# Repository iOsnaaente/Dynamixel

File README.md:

# Dynamixel

Dispositório pessoal para guardar códigos para Atuadores Dynamixel.

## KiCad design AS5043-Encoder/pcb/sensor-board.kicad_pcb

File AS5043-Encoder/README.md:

AS5043-Encoder
==============

This repos contains all the plans and software necessary to build a magnetic rotary encoder using the AS4053.

The setup for this chip is rather simple,
you need a few external components and a neodymium magnet that is attached to your rotating axis.
Then the sensor is placed below the magnet.
Since it uses the magnetic field neither dirt nor light will be a problem.
The sensor will output the angle of the magnet relative to a programmable starting position via analogue output
or via a [SSI](https://en.wikipedia.org/wiki/Synchronous_Serial_Interface)-Style interface.
(See the datasheet for details.)
With 10bit resolution it should be theoretically possible to measure the current angle in 0.35° steps.

The guys at austria microsystems were kind enough to send me 3 AS5043 and 3 AS5030 (similar part 8bit resolution).
*Big thanks to them.*

Mechanical Parts
----------------
There are 2 plans available :

* A version that can be build using a lathe
* A 3D printable version created with open scad
* A 3D printable version created with freecad

The plans for the first version can be found in the repo directory [chasis/lathe](chasis/lathe).
You can simply print out the pdfs and hand them over to someone who has access to a lathe.
He or she should know what to do with them.

For the 3D printable versions simply run the stl files through your 3D printing toolchain.
The 3D printable versions can be found in [chasis/3d_printable_scad](chasis/3d_printable_scad)
and [chasis/3d_printable_freecad](chasis/3d_printable_freecad).

You will also need some M3 screws and nuts which you should find in your favorite hardware store.
For the magnets I'd recommend browsing ebay for 5mmx5mmx5mm neodym magnet cubes.
The ball bearing you'll need is a common 6200Z bearing.
Again try your hardware store or ebay.
There you'll possible also find some M3 5mm long distance bolts, that are used in the lathe version of the chassis.

Software
--------
The software part required some tricks to get it working.
Comparing the signal diagrams for SPI in Atmels datasheet and for *SSI* in the AS5043 a small problem becomes obvious.
The AS5043 needs a clock signal that is high in idle stage and the bits will be shifted out on the positive clock edge.
That sounds very much like the SPI mode 3 in Atmel-speech: Clock high on idle and data will be read on every rising edge.
Leaving us with one problem: The Atmel hardware SPI can read the miso pin only at a clock edge.
As mentioned before data is sampled at the rising edge for mode 3.
So shifting out and reading would be done almost synchronous and due to signal rise and fall times this will probably fail 90% of the time.

The solution is to use mode 2: Clock high on idle and bits are read at the falling edge.
Now we have a different problem.
The first bit will be read before it was shifted out by the AS5043.
Using AVR SPI it is possible to read one byte at time, so two read cycles are required to read the full 16bit encoder output.

The first byte read in mode 2 will look like this:

| Bit 7       | Bit 6 | Bit 5 | Bit 4  | Bit 3 | Bit 2 | Bit 1 | Bit 0 |
|-------------|-------|-------|--------|-------|-------|-------|-------|
| **garbage** | D9    | D8    | D7     | D6    | D5    | D4    | D3    |

Reading the next 8bit will work fine since the 8th bit was shifted out on the last rising edge after reading the first 7 bit.
It will be read as the bit in on the falling edge for the next byte,
which looks like this:

| Bit 7 | Bit 6 | Bit 5 | Bit 4  | Bit 3 | Bit 2 | Bit 1   | Bit 0   |
|-------|-------|-------|--------|-------|-------|---------|---------|
| D2    | D1    | D0    | OCF    | COF   | LIN   | MAG INC | MAG DEC |

Everything after the *D0*-bit is status information needed in order to decide whether the measurement was valid.
Unfortunately important status bit is still missing.
The 16th bit contains the parity information required to check against transmission errors.
It is shifted out on the last rising edge when reading the second byte. Since the clock line is high afterwards,
the data line will stay on the 16th bits level until the next read is performed.
It can read by manually checking the *MISO* pins state.
The rest is just nifty bit shifting.

It is also important not to use the SS of the AVR mcu for chip select,
since this pin will change to high after reading the first byte, which causes the AS5043 to reset its *SSI* interface.

The code for this can be found in [AS5043.c](firmware/lib/AS5043.c) and in [AS5043.h](firmware/lib/include/AS5043.h).

A simple code for testing can be found in the directory [firmware/demo](firmware/demo).
main.c contains code for an Atmega8 or Atmega328 that reads the encoder, calculates the rotation in degrees and sends out using the uart.
cube.py is a simple receiving is the receiving part running on your computer.
It uses PyOpenGL to display a wireframe cube and rotate it according to the encoders rotation value.

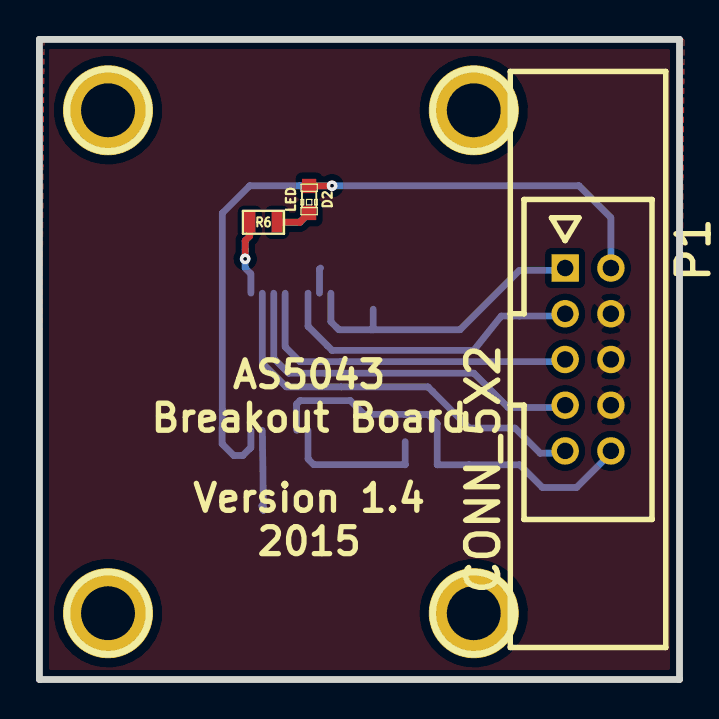
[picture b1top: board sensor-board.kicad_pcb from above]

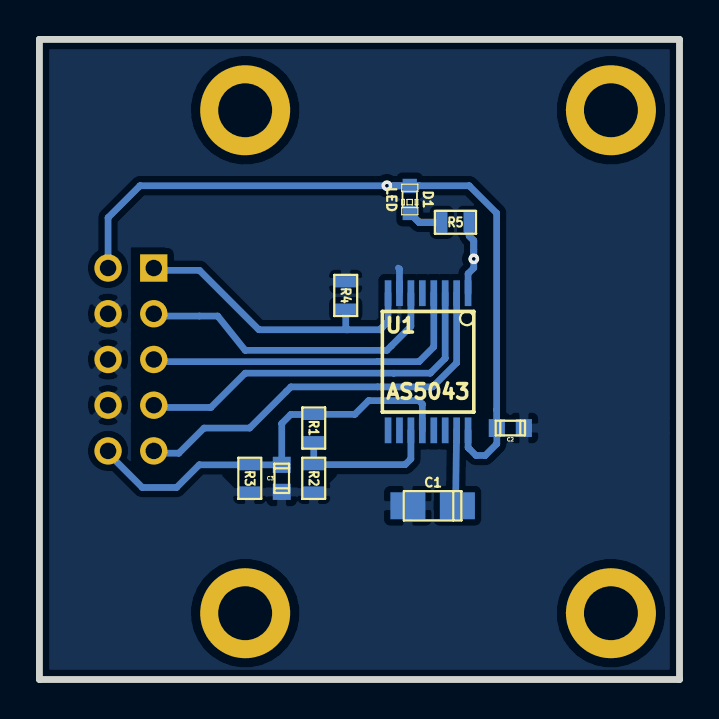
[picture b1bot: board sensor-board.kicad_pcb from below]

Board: 2 copper layers, 35.6 x 35.6 mm, 13 parts (10 on the bottom side), 13 nets.

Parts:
C1: 5uF; c_tant_A
C2: 100nF; c_0603
C3: 100pf; c_0603
D1, D2: LED; LED-0603
P1: CONN_5X2; he10-lock
R1, R2: 33k; SM0603
R3: 47k; SM0603
R4: 10k; SM0603
R5, R6: 1k; SM0603
U1: AS5043; SSOP16_WIDE

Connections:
+5V: C2.1, D1.1, D2.1, P1.2, U1.16
/CLK: P1.5, U1.4
/CS: P1.7, U1.3
/DO: P1.3, U1.6
/MODE: P1.9, U1.2
/PROG: P1.1, R4.1, U1.8
GND: C1.2, C2.2, C3.2, P1.4, P1.6, P1.8, R2.2, R3.2, R4.2, U1.7
unnamed: C1.1, U1.15
unnamed: C3.1, P1.10, R1.1, R3.1, U1.12
unnamed: D1.2, R5.1
unnamed: D2.2, R6.1
unnamed: R1.2, R2.1, U1.11
unnamed: R5.2, R6.2, U1.1

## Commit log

2020-12-14 Add code1.py to control the actuator and the module Serial to read the serial ports
2020-12-14 correção
2020-12-15 Att parametros
2020-12-24 backup
2020-12-28 Create an interface with dearpygui
